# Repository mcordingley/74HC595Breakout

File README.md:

# 74HC595Breakout
74HC595 breakout board that drives an ULN2803 Darlington array for added power.

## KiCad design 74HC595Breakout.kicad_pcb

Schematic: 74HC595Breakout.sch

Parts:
C1: 100nF; C_Disc_D4.7mm_W2.5mm_P5.00mm
J1: Input; PinHeader_1x07_P2.54mm_Vertical
J2: Chain; PinHeader_1x07_P2.54mm_Vertical
J3: Output; PinHeader_2x08_P2.54mm_Vertical
J4: Load Power; PinHeader_1x02_P2.54mm_Vertical
JP1: SRCLR Override; SolderJumper-2_P1.3mm_Bridged_Pad1.0x1.5mm
JP2: OE Override; SolderJumper-2_P1.3mm_Bridged_Pad1.0x1.5mm
JP3: Power Select; SolderJumper-2_P1.3mm_Bridged_Pad1.0x1.5mm
U1: 74HC595; DIP-16_W7.62mm
U2: ULN2803A; DIP-18_W7.62mm

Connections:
/OE: J1.4, J2.4, JP2.1 (A), U1.13 (~OE)
/SRCLR: J1.7, J2.7, JP1.2 (B), U1.10 (~SRCLR)
GND: C1.2, J1.1, J2.1, J4.1, JP2.2 (B), U1.8 (GND), U2.9 (GND)
unnamed: J1.3, U1.14 (SER)
unnamed: J1.5, J2.5, U1.12 (RCLK)
unnamed: J1.6, J2.6, U1.11 (SRCLK)
unnamed: J2.3, U1.9 (QH')
unnamed: J3.1, U2.18 (O1)
unnamed: J3.2, U2.17 (O2)
unnamed: J3.3, U2.16 (O3)
unnamed: J3.4, U2.15 (O4)
unnamed: J3.5, U2.14 (O5)
unnamed: J3.6, U2.13 (O6)
unnamed: J3.7, U2.12 (O7)
unnamed: J3.8, U2.11 (O8)
unnamed: U1.1 (QB), U2.2 (I2)
unnamed: U1.2 (QC), U2.3 (I3)
unnamed: U1.3 (QD), U2.4 (I4)
unnamed: U1.4 (QE), U2.5 (I5)
unnamed: U1.5 (QF), U2.6 (I6)
unnamed: U1.6 (QG), U2.7 (I7)
unnamed: U1.7 (QH), U2.8 (I8)
unnamed: U1.15 (QA), U2.1 (I1)
VCC: C1.1, J1.2, J2.2, JP1.1 (A), JP3.1 (A), U1.16 (VCC)

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
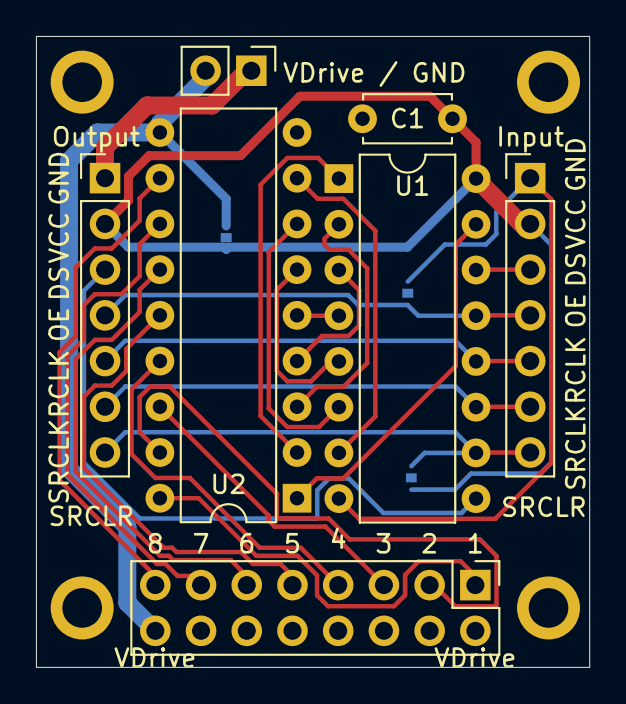
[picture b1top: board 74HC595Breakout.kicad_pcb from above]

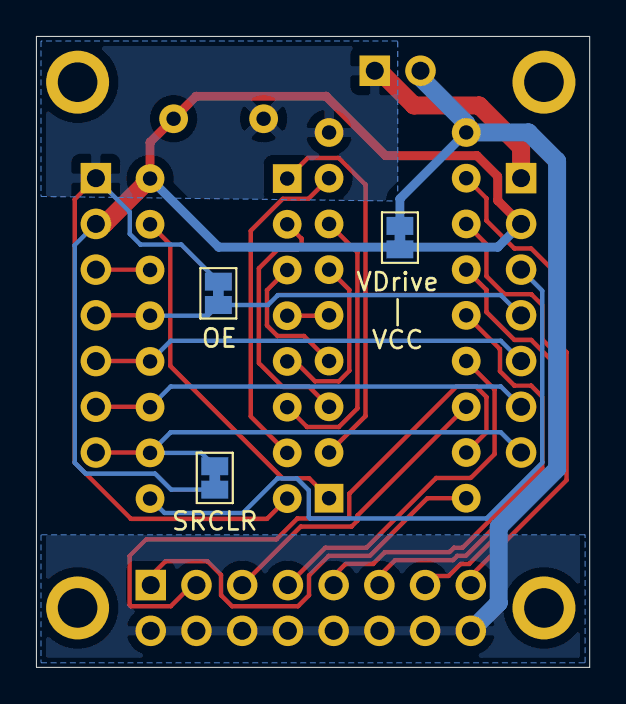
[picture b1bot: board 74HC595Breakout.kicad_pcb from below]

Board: 2 copper layers, 30.7 x 35.1 mm, 10 parts (3 on the bottom side), 25 nets.

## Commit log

2020-09-05 Commit project files.
2020-10-05 Update for inductive isolation and higher current capacity.
2020-10-21 Update with wider traces for power and crowded but informative labels.
